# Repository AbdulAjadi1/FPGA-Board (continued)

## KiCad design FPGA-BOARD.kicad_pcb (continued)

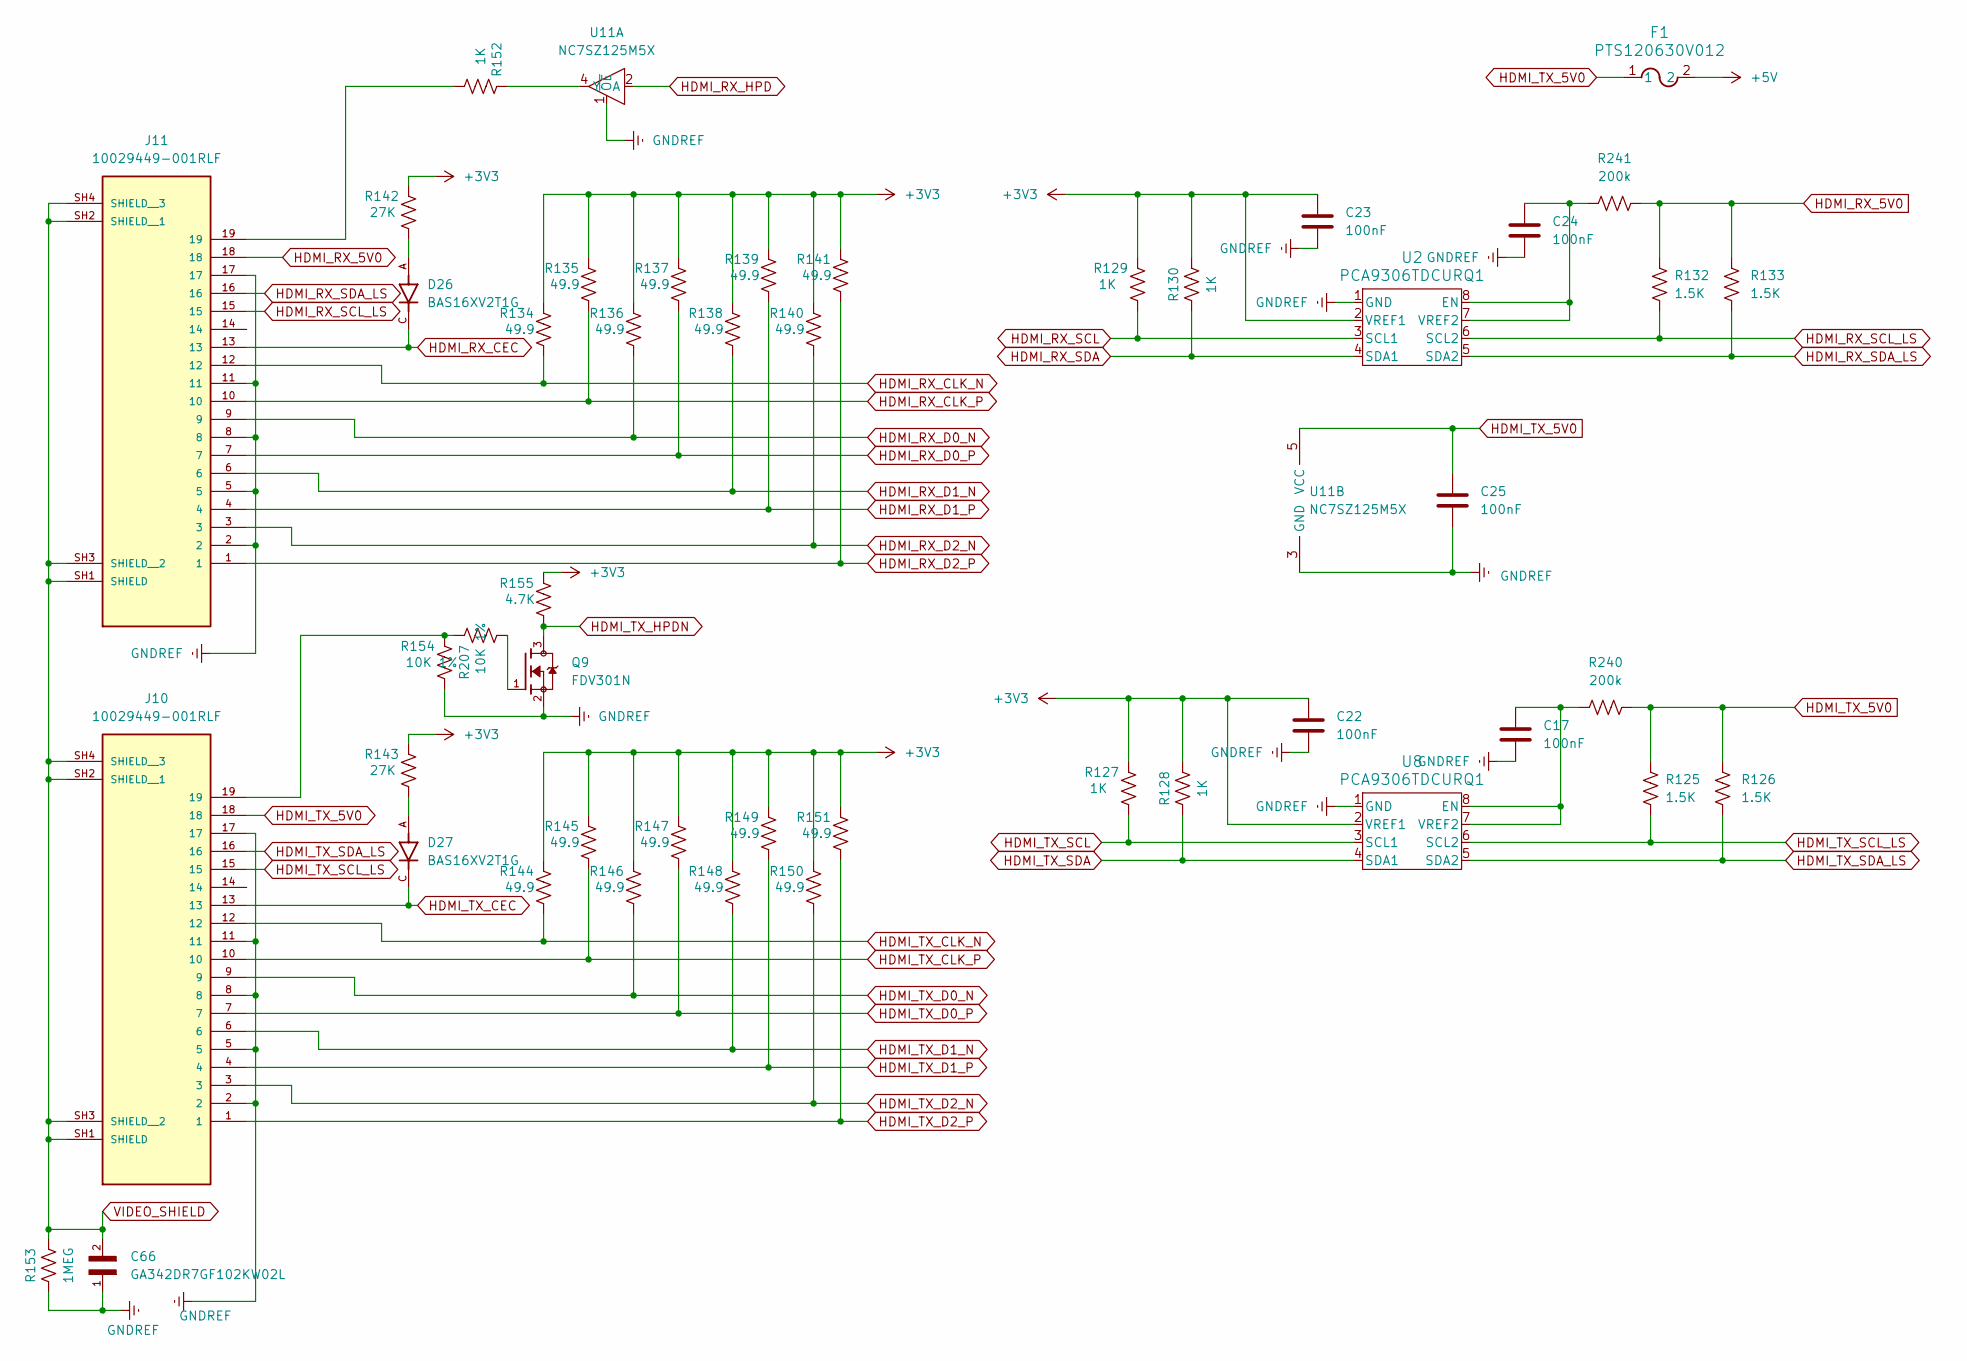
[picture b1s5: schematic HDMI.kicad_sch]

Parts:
C17, C22, C23, C24, C25: 100nF; C_0201_0603Metric; LCSC PN c307380
C66: GA342DR7GF102KW02L; CAPC4520X220N; LCSC PN C237595
D26, D27: BAS16XV2T1G; SODFL1608X70N; PARTREV 10; LCSC PN C152479
F1: PTS120630V012; LCSC PN C2442491
J10, J11: 10029449-001RLF; AMPHENOL_10029449-001RLF; PARTREV Y
Q9: FDV301N; PARTREV 8; LCSC PN C15310
R125, R126, R132, R133: 1.5K; R_0402; LCSC PN C114759
R127, R128, R129, R130, R152: 1K; R_0402; LCSC PN C106235
R134, R135, R136, R137, R138, R139, R140, R141, R144, R145, R146, R147, R148, R149, R150, R151: 49.9; R_0402; LCSC PN C87044
R142, R143: 27K; R_0402; LCSC PN C138022
R153: 1MEG; R_0402; LCSC PN C138033
R154, R207: 10K 1%; R_0402; LCSC PN C60490
R155: 4.7K; R_0201_0603Metric; LCSC PN C138135
R240, R241: 200k; R_0402; LCSC PN c114763
U2, U8: PCA9306TDCURQ1; DCU8; LCSC PN C33196
U11: NC7SZ125M5X; SC-74A_318BQ_ONS; LCSC PN C7420

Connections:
+3V3: C22.1, C23.1, R127.2, R128.2, R129.2, R130.2, R134.2, R135.2, R136.2, R137.2, R138.2, R139.2, R140.2, R141.2, R142.2, R143.2, R144.2, R145.2, R146.2, R147.2, R148.2, R149.2, R150.2, R151.2, R155.2, U2.2 (VREF1), U8.2 (VREF1); also elsewhere on the board
+5V: F1.2; also elsewhere on the board
GNDREF: C17.2, C22.2, C23.2, C24.2, C25.2, C66.1, J10.2, J10.5, J10.8, J10.11, J10.17, J11.2, J11.5, J11.8, J11.11, J11.17, Q9.2, R153.1, R154.1, U2.1 (GND), U8.1 (GND), U11.1 (~OE), U11.3 (GND); also elsewhere on the board
HDMI_RX_5V0: J11.18, R132.2, R133.2, R241.1
HDMI_RX_CEC: D26.C, J11.13; also elsewhere on the board
HDMI_RX_CLK_N: J11.12, R134.1; also elsewhere on the board
HDMI_RX_CLK_P: J11.10, R135.1; also elsewhere on the board
HDMI_RX_D0_N: J11.9, R136.1; also elsewhere on the board
HDMI_RX_D0_P: J11.7, R137.1; also elsewhere on the board
HDMI_RX_D1_N: J11.6, R138.1; also elsewhere on the board
HDMI_RX_D1_P: J11.4, R139.1; also elsewhere on the board
HDMI_RX_D2_N: J11.3, R140.1; also elsewhere on the board
HDMI_RX_D2_P: J11.1, R141.1; also elsewhere on the board
HDMI_RX_HPD: U11.2 (A); also elsewhere on the board
HDMI_RX_SCL: R129.1, U2.3 (SCL1); also elsewhere on the board
HDMI_RX_SCL_LS: J11.15, R132.1, U2.6 (SCL2)
HDMI_RX_SDA: R130.1, U2.4 (SDA1); also elsewhere on the board
HDMI_RX_SDA_LS: J11.16, R133.1, U2.5 (SDA2)
HDMI_TX_5V0: C25.1, F1.1, J10.18, R125.2, R126.2, R240.1, U11.5 (VCC)
HDMI_TX_CEC: D27.C, J10.13; also elsewhere on the board
HDMI_TX_CLK_N: J10.12, R144.1; also elsewhere on the board
HDMI_TX_CLK_P: J10.10, R145.1; also elsewhere on the board
HDMI_TX_D0_N: J10.9, R146.1; also elsewhere on the board
HDMI_TX_D0_P: J10.7, R147.1; also elsewhere on the board
HDMI_TX_D1_N: J10.6, R148.1; also elsewhere on the board
HDMI_TX_D1_P: J10.4, R149.1; also elsewhere on the board
HDMI_TX_D2_N: J10.3, R150.1; also elsewhere on the board
HDMI_TX_D2_P: J10.1, R151.1; also elsewhere on the board
HDMI_TX_HPDN: Q9.3, R155.1; also elsewhere on the board
HDMI_TX_SCL: R127.1, U8.3 (SCL1); also elsewhere on the board
HDMI_TX_SCL_LS: J10.15, R125.1, U8.6 (SCL2)
HDMI_TX_SDA: R128.1, U8.4 (SDA1); also elsewhere on the board
HDMI_TX_SDA_LS: J10.16, R126.1, U8.5 (SDA2)
unnamed: D26.A, R142.1
unnamed: D27.A, R143.1
unnamed: J10.19, R154.2, R207.2
unnamed: J11.19, R152.1
unnamed: Q9.1, R207.1
unnamed: C24.1, R241.2, U2.7 (VREF2), U2.8 (EN)
unnamed: C17.1, R240.2, U8.7 (VREF2), U8.8 (EN)
unnamed: R152.2, U11.4 (Y)
VIDEO_SHIELD: C66.2, J10.SH1 (SHIELD), J10.SH2 (SHIELD__1), J10.SH3 (SHIELD__2), J10.SH4 (SHIELD__3), J11.SH1 (SHIELD), J11.SH2 (SHIELD__1), J11.SH3 (SHIELD__2), J11.SH4 (SHIELD__3), R153.2

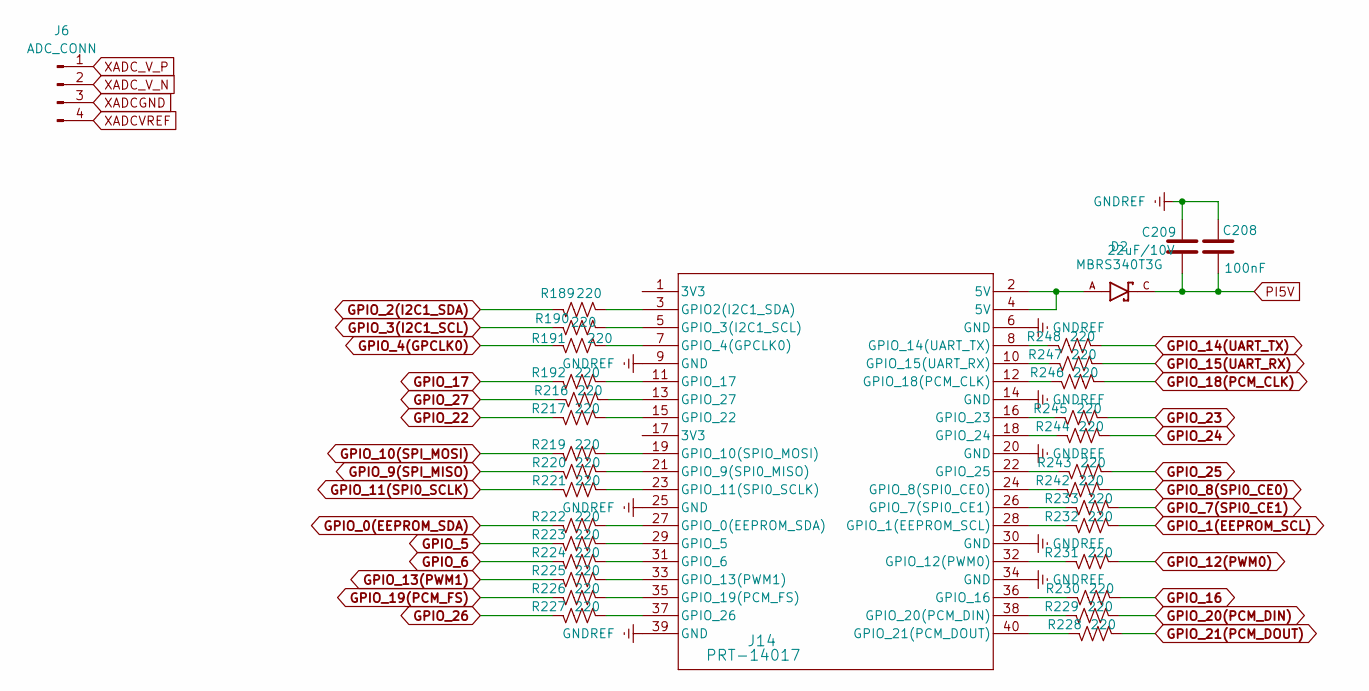
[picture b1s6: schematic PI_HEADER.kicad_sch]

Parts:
C208: 100nF; C_0201_0603Metric; LCSC PN c307380
C209: 22uF/10V; C_0805; LCSC PN C602037
D2: MBRS340T3G; DIOM7959X261N; PARTREV 14; LCSC PN C40326
J6: ADC_CONN; PinSocket_1x04_P2.54mm_Vertical
J14: PRT-14017; CONN_PRT-14017_SPK
R189, R190, R191, R192, R216, R217, R219, R220, R221, R222, R223, R224, R225, R226, R227, R228, R229, R230, R231, R232, R233, R242, R243, R244, R245, R246, R247, R248: 220; R_0402; LCSC PN C112291

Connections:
GNDREF: C208.1, C209.1, J14.6 (GND), J14.9 (GND), J14.14 (GND), J14.20 (GND), J14.25 (GND), J14.30 (GND), J14.34 (GND), J14.39 (GND); also elsewhere on the board
GPIO_0(EEPROM_SDA): R222.1; also elsewhere on the board
GPIO_1(EEPROM_SCL): R232.2; also elsewhere on the board
GPIO_2(I2C1_SDA): R189.1; also elsewhere on the board
GPIO_3(I2C1_SCL): R190.1; also elsewhere on the board
GPIO_4(GPCLK0): R191.1; also elsewhere on the board
GPIO_5: R223.1; also elsewhere on the board
GPIO_6: R224.1; also elsewhere on the board
GPIO_7(SPI0_CE1): R233.2; also elsewhere on the board
GPIO_8(SPI0_CE0): R242.2; also elsewhere on the board
GPIO_9(SPI_MISO): R220.1; also elsewhere on the board
GPIO_10(SPI_MOSI): R219.1; also elsewhere on the board
GPIO_11(SPI0_SCLK): R221.1; also elsewhere on the board
GPIO_12(PWM0): R231.2; also elsewhere on the board
GPIO_13(PWM1): R225.1; also elsewhere on the board
GPIO_14(UART_TX): R248.2; also elsewhere on the board
GPIO_15(UART_RX): R247.2; also elsewhere on the board
GPIO_16: R230.2; also elsewhere on the board
GPIO_17: R192.1; also elsewhere on the board
GPIO_18(PCM_CLK): R246.2; also elsewhere on the board
GPIO_19(PCM_FS): R226.1; also elsewhere on the board
GPIO_20(PCM_DIN): R229.2; also elsewhere on the board
GPIO_21(PCM_DOUT): R228.2; also elsewhere on the board
GPIO_22: R217.1; also elsewhere on the board
GPIO_23: R245.2; also elsewhere on the board
GPIO_24: R244.2; also elsewhere on the board
GPIO_25: R243.2; also elsewhere on the board
GPIO_26: R227.1; also elsewhere on the board
GPIO_27: R216.1; also elsewhere on the board
unnamed: D2.A, J14.2 (5V), J14.4 (5V)
unnamed: J14.3 (GPIO2(I2C1_SDA)), R189.2
unnamed: J14.27 (GPIO_0(EEPROM_SDA)), R222.2
unnamed: J14.28 (GPIO_1(EEPROM_SCL)), R232.1
unnamed: J14.5 (GPIO_3(I2C1_SCL)), R190.2
unnamed: J14.7 (GPIO_4(GPCLK0)), R191.2
unnamed: J14.29 (GPIO_5), R223.2
unnamed: J14.31 (GPIO_6), R224.2
unnamed: J14.26 (GPIO_7(SPI0_CE1)), R233.1
unnamed: J14.24 (GPIO_8(SPI0_CE0)), R242.1
unnamed: J14.21 (GPIO_9(SPI0_MISO)), R220.2
unnamed: J14.19 (GPIO_10(SPIO_MOSI)), R219.2
unnamed: J14.23 (GPIO_11(SPI0_SCLK)), R221.2
unnamed: J14.32 (GPIO_12(PWM0)), R231.1
unnamed: J14.33 (GPIO_13(PWM1)), R225.2
unnamed: J14.8 (GPIO_14(UART_TX)), R248.1
unnamed: J14.10 (GPIO_15(UART_RX)), R247.1
unnamed: J14.36 (GPIO_16), R230.1
unnamed: J14.11 (GPIO_17), R192.2
unnamed: J14.12 (GPIO_18(PCM_CLK)), R246.1
unnamed: J14.35 (GPIO_19(PCM_FS)), R226.2
unnamed: J14.38 (GPIO_20(PCM_DIN)), R229.1
unnamed: J14.40 (GPIO_21(PCM_DOUT)), R228.1
unnamed: J14.15 (GPIO_22), R217.2
unnamed: J14.16 (GPIO_23), R245.1
unnamed: J14.18 (GPIO_24), R244.1
unnamed: J14.22 (GPIO_25), R243.1
unnamed: J14.37 (GPIO_26), R227.2
unnamed: J14.13 (GPIO_27), R216.2
PI5V: C208.2, C209.2, D2.C; also elsewhere on the board
XADCGND: J6.3; also elsewhere on the board
XADCVREF: J6.4; also elsewhere on the board
XADC_V_N: J6.2; also elsewhere on the board
XADC_V_P: J6.1; also elsewhere on the board

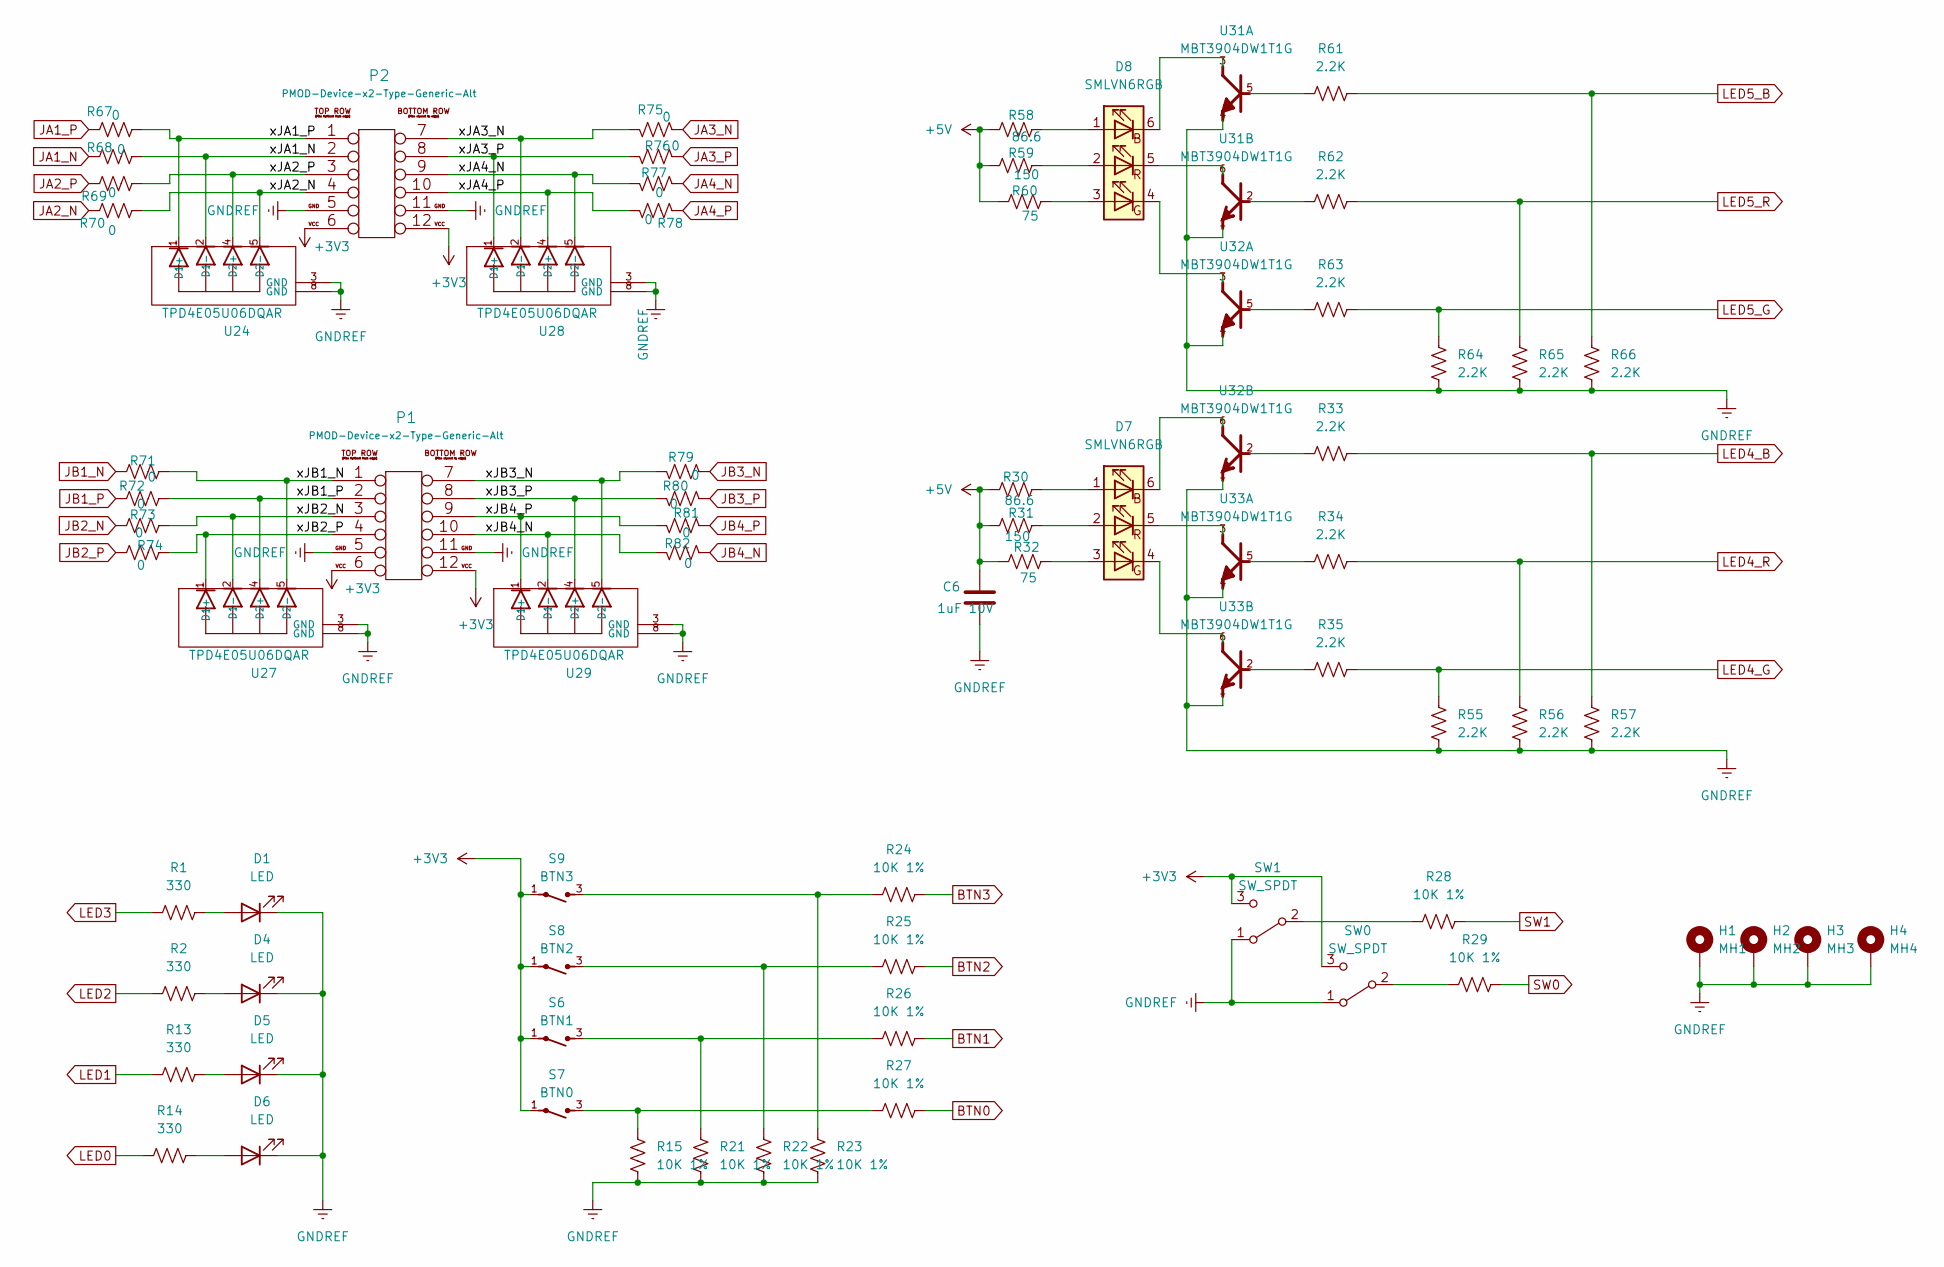
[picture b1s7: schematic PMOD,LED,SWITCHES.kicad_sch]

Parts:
C6: 1uF 10V; C_0402; LCSC PN C52923
D1, D4, D5, D6: LED; LED_0402_1005Metric; LCSC PN C130723
D7, D8: SMLVN6RGB; LED_SMLV56_ROM; LCSC PN C20110230
H1: MH1; MountingHole_2.2mm_M2_Pad
H2: MH2; MountingHole_2.2mm_M2_Pad
H3: MH3; MountingHole_2.2mm_M2_Pad
H4: MH4; MountingHole_2.2mm_M2_Pad
P1, P2: PMOD-Device-x2-Type-Generic-Alt; CONN_PPPC062LJBN-RC_SUL
R1, R2, R13, R14: 330; R_0402; LCSC PN C105875
R15, R21, R22, R23, R24, R25, R26, R27, R28, R29: 10K 1%; R_0402; LCSC PN C60490
R30, R58: 86.6; R_0402; LCSC PN C830266
R31, R59: 150; R_0402; LCSC PN C138054
R32, R60: 75; R_0402; LCSC PN C114757
R33, R34, R35, R55, R56, R57, R61, R62, R63, R64, R65, R66: 2.2K; R_0402; LCSC PN c114762
R67, R68, R69, R70, R71, R72, R73, R74, R75, R76, R77, R78, R79, R80, R81, R82: 0; R_0402; LCSC PN C106231
S6: BTN1; TS-1002S-050xxC_XNP; LCSC PN C455110
S7: BTN0; TS-1002S-050xxC_XNP; LCSC PN C455110
S8: BTN2; TS-1002S-050xxC_XNP; LCSC PN C455110
S9: BTN3; TS-1002S-050xxC_XNP; LCSC PN C455110
SW0, SW1: SW_SPDT; SW_EG1218
U24, U27, U28, U29: TPD4E05U06DQAR; IC_TPD4E05U06DQAR; PARTREV N; LCSC PN C138714
U31, U32, U33: MBT3904DW1T1G; SOT236; LCSC PN C110150

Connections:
+3V3: P1.6, P1.12, P2.6, P2.12, S6.1, S7.1, S8.1, S9.1, SW0.3 (C), SW1.3 (C); also elsewhere on the board
+5V: C6.1, R30.1, R31.1, R32.1, R58.1, R59.1, R60.1; also elsewhere on the board
/PMOD, LED, SWITCHES/xJA1_N: P2.2, R68.2, U24.2 (D1-)
/PMOD, LED, SWITCHES/xJA1_P: P2.1, R67.2, U24.1 (D1+)
/PMOD, LED, SWITCHES/xJA2_N: P2.4, R70.2, U24.5 (D2-)
/PMOD, LED, SWITCHES/xJA2_P: P2.3, R69.2, U24.4 (D2+)
/PMOD, LED, SWITCHES/xJA3_N: P2.7, R75.2, U28.2 (D1-)
/PMOD, LED, SWITCHES/xJA3_P: P2.8, R76.2, U28.1 (D1+)
/PMOD, LED, SWITCHES/xJA4_N: P2.9, R77.2, U28.5 (D2-)
/PMOD, LED, SWITCHES/xJA4_P: P2.10, R78.2, U28.4 (D2+)
/PMOD, LED, SWITCHES/xJB1_N: P1.1, R71.2, U27.5 (D2-)
/PMOD, LED, SWITCHES/xJB1_P: P1.2, R72.2, U27.4 (D2+)
/PMOD, LED, SWITCHES/xJB2_N: P1.3, R73.2, U27.2 (D1-)
/PMOD, LED, SWITCHES/xJB2_P: P1.4, R74.2, U27.1 (D1+)
/PMOD, LED, SWITCHES/xJB3_N: P1.7, R79.2, U29.5 (D2-)
/PMOD, LED, SWITCHES/xJB3_P: P1.8, R80.2, U29.4 (D2+)
/PMOD, LED, SWITCHES/xJB4_N: P1.10, R82.2, U29.2 (D1-)
/PMOD, LED, SWITCHES/xJB4_P: P1.9, R81.2, U29.1 (D1+)
BTN0: R27.2; also elsewhere on the board
BTN1: R26.2; also elsewhere on the board
BTN2: R25.2; also elsewhere on the board
BTN3: R24.2; also elsewhere on the board
GNDREF: C6.2, D1.1 (K), D4.1 (K), D5.1 (K), D6.1 (K), H1.1, H2.1, H3.1, H4.1, P1.5, P1.11, P2.5, P2.11, R15.2, R21.2, R22.2, R23.2, R55.1, R56.1, R57.1, R64.1, R65.1, R66.1, SW0.1 (A), SW1.1 (A), U24.3 (GND), U24.8 (GND), U27.3 (GND), U27.8 (GND), U28.3 (GND), U28.8 (GND), U29.3 (GND), U29.8 (GND), U31.1, U31.4, U32.1, U32.4, U33.1, U33.4; also elsewhere on the board
JA1_N: R68.1; also elsewhere on the board
JA1_P: R67.1; also elsewhere on the board
JA2_N: R70.1; also elsewhere on the board
JA2_P: R69.1; also elsewhere on the board
JA3_N: R75.1; also elsewhere on the board
JA3_P: R76.1; also elsewhere on the board
JA4_N: R77.1; also elsewhere on the board
JA4_P: R78.1; also elsewhere on the board
JB1_N: R71.1; also elsewhere on the board
JB1_P: R72.1; also elsewhere on the board
JB2_N: R73.1; also elsewhere on the board
JB2_P: R74.1; also elsewhere on the board
JB3_N: R79.1; also elsewhere on the board
JB3_P: R80.1; also elsewhere on the board
JB4_N: R82.1; also elsewhere on the board
JB4_P: R81.1; also elsewhere on the board
LED0: R14.1; also elsewhere on the board
LED1: R13.1; also elsewhere on the board
LED2: R2.1; also elsewhere on the board
LED3: R1.1; also elsewhere on the board
LED4_B: R33.2, R57.2; also elsewhere on the board
LED4_G: R35.2, R55.2; also elsewhere on the board
LED4_R: R34.2, R56.2; also elsewhere on the board
LED5_B: R61.2, R66.2; also elsewhere on the board
LED5_G: R63.2, R64.2; also elsewhere on the board
LED5_R: R62.2, R65.2; also elsewhere on the board
unnamed: D1.2 (A), R1.2
unnamed: D4.2 (A), R2.2
unnamed: D5.2 (A), R13.2
unnamed: D6.2 (A), R14.2
unnamed: D7.1 (BA), R30.2
unnamed: D7.6 (BK), U32.6
unnamed: D7.3 (GA), R32.2
unnamed: D7.4 (GK), U33.6
unnamed: D7.2 (RA), R31.2
unnamed: D7.5 (RK), U33.3
unnamed: D8.1 (BA), R58.2
unnamed: D8.6 (BK), U31.3
unnamed: D8.3 (GA), R60.2
unnamed: D8.4 (GK), U32.3
unnamed: D8.2 (RA), R59.2
unnamed: D8.5 (RK), U31.6
unnamed: R15.1, R27.1, S7.3
unnamed: R21.1, R26.1, S6.3
unnamed: R22.1, R25.1, S8.3
unnamed: R23.1, R24.1, S9.3
unnamed: R33.1, U32.2
unnamed: R34.1, U33.5
unnamed: R35.1, U33.2
unnamed: R61.1, U31.5
unnamed: R62.1, U31.2
unnamed: R63.1, U32.5
unnamed: R29.1, SW0.2 (B)
unnamed: R28.1, SW1.2 (B)
SW0: R29.2; also elsewhere on the board
SW1: R28.2; also elsewhere on the board

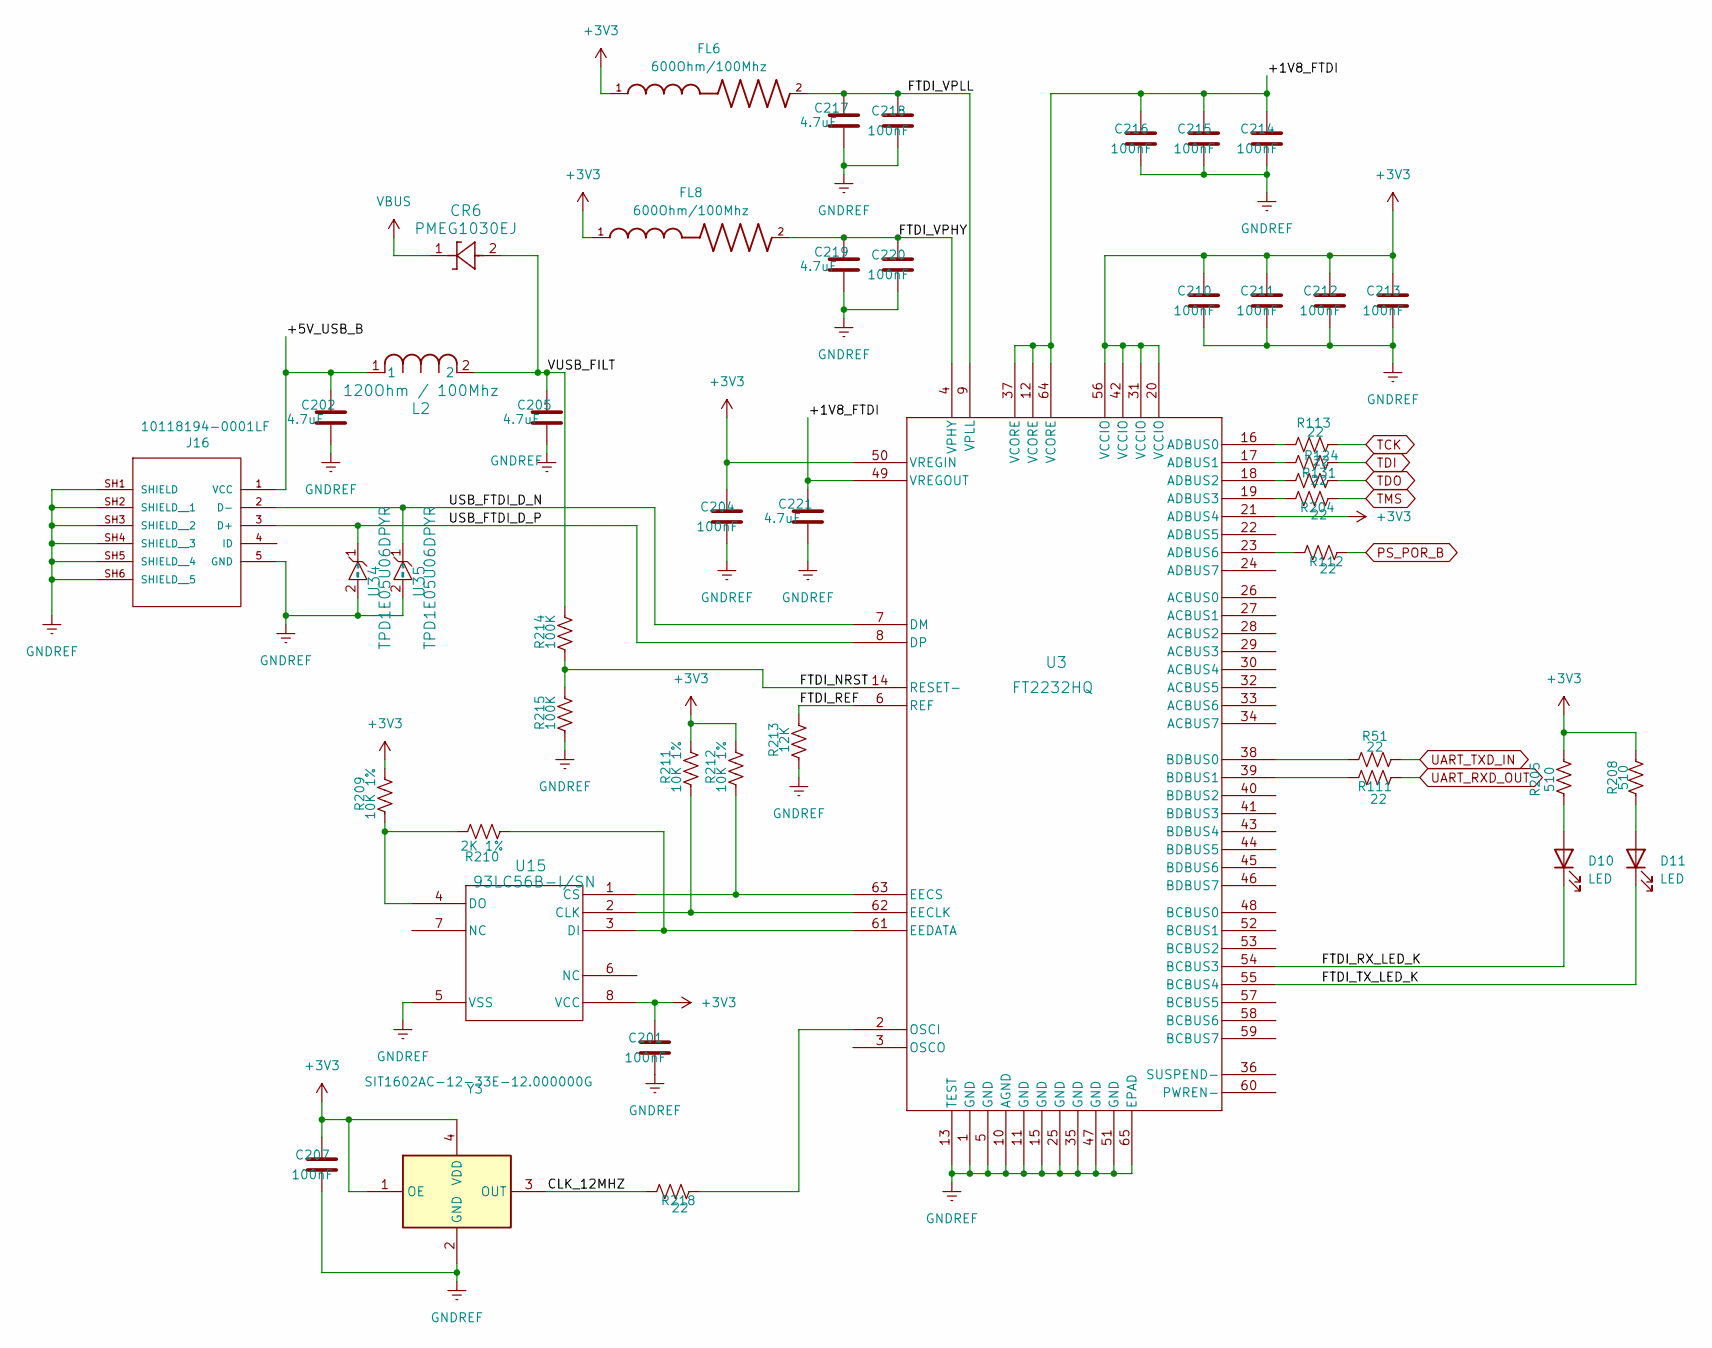
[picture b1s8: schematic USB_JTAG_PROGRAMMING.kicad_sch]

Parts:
C201, C204, C207, C210, C211, C212, C213, C214, C215, C216, C218, C220: 100nF; C_0201_0603Metric; LCSC PN c307380
C202, C205, C217, C219, C221: 4.7uF; C_0402; LCSC PN C2858031
CR6: PMEG1030EJ; SOD323F_NXP; LCSC PN C133633
D10, D11: LED; LED_0402_1005Metric; LCSC PN C130723
FL6, FL8: 600Ohm/100Mhz; BEADC1608X95N; LCSC PN C19330
J16: 10118194-0001LF; AMPHENOL_10118194-0001LF; PARTREV D
L2: 120Ohm / 100Mhz; IND_BLM18_0603_MUR; LCSC PN C14709
R51, R111, R112, R113, R124, R131, R204, R218: 22; R_0201_0603Metric; LCSC PN C270355
R205, R208: 510; R_0201_0603Metric; LCSC PN C18164337
R209, R211, R212: 10K 1%; R_0402; LCSC PN C60490
R210: 2K 1%; R_0402; LCSC PN C60488
R213: 12K; R_0201_0603Metric; LCSC PN C2092166
R214, R215: 100K; R_0402; LCSC PN C60491
U3: FT2232HQ; 64QFN_FT2232HQ_FTD; LCSC PN C3025148
U15: 93LC56B-I/SN; SOIC8-N_MC_MCH; LCSC PN C183620
U34, U35: TPD1E05U06DPYR; DIO_TPD1E05U06DPYR; LCSC PN C436349
Y3: SIT1602AC-12-33E-12.000000G; SIT1602AC1233E12000000G; Mouser Part Number 788-1602AC1233E12.G

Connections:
+3V3: C201.1, C204.1, C207.1, C210.1, C211.1, C212.1, C213.1, FL6.1, FL8.1, R205.2, R208.2, R209.2, R211.2, R212.2, U3.20 (VCCIO), U3.21 (ADBUS4), U3.31 (VCCIO), U3.42 (VCCIO), U3.50 (VREGIN), U3.56 (VCCIO), U15.8 (VCC), Y3.1 (OE), Y3.4 (VDD); also elsewhere on the board
/USB_JTAG_PROGRAMMING/+1V8_FTDI: C214.1, C215.1, C216.1, C221.1, U3.12 (VCORE), U3.37 (VCORE), U3.49 (VREGOUT), U3.64 (VCORE)
/USB_JTAG_PROGRAMMING/+5V_USB_B: C202.1, J16.1 (VCC), L2.1
/USB_JTAG_PROGRAMMING/CLK_12MHZ: R218.1, Y3.3 (OUT)
/USB_JTAG_PROGRAMMING/FTDI_NRST: R214.1, R215.2, U3.14 (RESET-)
/USB_JTAG_PROGRAMMING/FTDI_REF: R213.2, U3.6 (REF)
/USB_JTAG_PROGRAMMING/FTDI_RX_LED_K: D10.1 (K), U3.54 (BCBUS3)
/USB_JTAG_PROGRAMMING/FTDI_TX_KED_K: D11.1 (K), U3.55 (BCBUS4)
/USB_JTAG_PROGRAMMING/FTDI_VPHY: C219.1, C220.1, FL8.2, U3.4 (VPHY)
/USB_JTAG_PROGRAMMING/FTDI_VPLL: C217.1, C218.1, FL6.2, U3.9 (VPLL)
/USB_JTAG_PROGRAMMING/USB_FTDI_D_N: J16.2 (D-), U3.7 (DM), U35.1 (I/O)
/USB_JTAG_PROGRAMMING/USB_FTDI_D_P: J16.3 (D+), U3.8 (DP), U34.1 (I/O)
/USB_JTAG_PROGRAMMING/VUSB_FILT: C205.1, CR6.2, L2.2, R214.2
GNDREF: C201.2, C202.2, C204.2, C205.2, C207.2, C210.2, C211.2, C212.2, C213.2, C214.2, C215.2, C216.2, C217.2, C218.2, C219.2, C220.2, C221.2, J16.5 (GND), J16.SH1 (SHIELD), J16.SH2 (SHIELD__1), J16.SH3 (SHIELD__2), J16.SH4 (SHIELD__3), J16.SH5 (SHIELD__4), J16.SH6 (SHIELD__5), R213.1, R215.1, U3.1 (GND), U3.5 (GND), U3.10 (AGND), U3.11 (GND), U3.13 (TEST), U3.15 (GND), U3.25 (GND), U3.35 (GND), U3.47 (GND), U3.51 (GND), U3.65 (EPAD), U15.5 (VSS), U34.2 (GND), U35.2 (GND), Y3.2 (GND); also elsewhere on the board
unnamed: D10.2 (A), R205.1
unnamed: D11.2 (A), R208.1
unnamed: R113.1, U3.16 (ADBUS0)
unnamed: R124.1, U3.17 (ADBUS1)
unnamed: R131.1, U3.18 (ADBUS2)
unnamed: R204.1, U3.19 (ADBUS3)
unnamed: R112.1, U3.23 (ADBUS6)
unnamed: R51.1, U3.38 (BDBUS0)
unnamed: R111.1, U3.39 (BDBUS1)
unnamed: R218.2, U3.2 (OSCI)
unnamed: R211.1, U3.62 (EECLK), U15.2 (CLK)
unnamed: R212.1, U3.63 (EECS), U15.1 (CS)
unnamed: R210.1, U3.61 (EEDATA), U15.3 (DI)
unnamed: R209.1, R210.2, U15.4 (DO)
PS_POR_B: R112.2; also elsewhere on the board
TCK: R113.2; also elsewhere on the board
TDI: R124.2; also elsewhere on the board
TDO: R131.2; also elsewhere on the board
TMS: R204.2; also elsewhere on the board
UART_RXD_OUT: R111.2; also elsewhere on the board
UART_TXD_IN: R51.2; also elsewhere on the board
VBUS: CR6.1; also elsewhere on the board

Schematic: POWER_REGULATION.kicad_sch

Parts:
C7, C20, C27: 4.7uF; C_0402; LCSC PN C2858031
C18, C19, C28, C32, C199, C234: 100nF; C_0201_0603Metric; LCSC PN c307380
C21: 1uF 10V; C_0402; LCSC PN C52923
C26: 470nF; C_0201_0603Metric; LCSC PN C5383023
C29: 22nF; C_0402; LCSC PN c337699
C30: 100nF 10V; C_0402; LCSC PN C77020
C31, C192, C193, C194, C195, C196, C197, C198: 10uF 10V; C_0805; LCSC PN C15850
CR7: BZT52C12-7-F; SOD123_DIO; LCSC PN C19077410
D37: SMBJ15CA-E3_52; DIOM5436X244N; Manufacturer_Part_Number SMBJ15CA-E3/52; LCSC PN C435933
FL2, FL5, FL9: 600Ohm/100Mhz; BEADC1608X95N; LCSC PN C19330
J1: PJ-102AH; CUI_PJ-102AH
J2: GND; PinHeader_1x01_P2.54mm_Vertical
J3: Conn_01x03_Pin; PinHeader_1x03_P2.54mm_Vertical
J17: Conn_01x02_Pin; PinHeader_1x02_P2.54mm_Vertical
J18: +3V3; PinHeader_1x01_P2.54mm_Vertical
J20: +1V5; PinHeader_1x01_P2.54mm_Vertical
J21: +1V0; PinHeader_1x01_P2.54mm_Vertical
J22: VCC_1V8IO; PinHeader_1x01_P2.54mm_Vertical
L4: NR5040T2R2N/2.2uH; IND_TAIYO_NR5040_TAY; LCSC PN C223063
Q7: DMG2305UX-13; DMG2305UX_13; PARTREV 09/2018; LCSC PN C144153
R83: 100K; R_0402; LCSC PN C60491
R84: 4.7k; R_0402; LCSC PN C105871
R85: 20K 1%; R_0402; LCSC PN C93942
R86, R89: 10K 1%; R_0402; LCSC PN C60490
R87: 13.3K/1%; R_0402; LCSC PN C274352
R88: 69.8K/1%; R_0402; LCSC PN C5126210
R90: 62k/1%; R_0402; LCSC PN C137950
R91: 0; R_0402; LCSC PN C106231
U14: TLV62130RGTT; LCSC PN C122479
U16: REF3012; SOT-23; LCSC PN C34674

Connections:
+1V0: J21.1; also elsewhere on the board
+1V5: J20.1; also elsewhere on the board
+1V8: C21.1, FL2.1; also elsewhere on the board
+3V3: C7.1, C19.1, FL9.1, J18.1; also elsewhere on the board
+5V: J3.2, J17.1, R85.1; also elsewhere on the board
/POWER_REGULATION/VUSB: J3.3, Q7.3
AVCC3V3: C20.1, C199.1, C234.1, FL9.2; also elsewhere on the board
EN_1: R85.2, R86.1; also elsewhere on the board
GNDREF: C7.2, C19.2, C20.2, C21.2, C28.2, C29.2, C30.2, C31.2, C192.2, C193.2, C194.2, C195.2, C196.2, C197.2, C198.2, C199.2, C234.2, D37.2, FL5.1, J1.2, J1.3, J2.1, R84.2, R86.2, R87.2, R89.2, U14.6 (AGND), U14.8 (DEF), U14.15 (PGND@1), U14.16 (PGND@2), U14.17 (GND), U14.18, U14.19, U14.20, U14.21, U14.22; also elsewhere on the board
unnamed: C27.2, CR7.2, Q7.1, R83.2, R84.1
unnamed: C28.1, R89.1, R90.2, U14.13 (EN)
unnamed: R87.1, R88.2, U14.5 (FB)
unnamed: R91.2, U14.7 (FSW)
unnamed: C29.1, U14.9 (SS/TR)
unnamed: L4.2, U14.1 (SW@1), U14.2 (SW@2), U14.3 (SW@3)
PI5V: J17.2; also elsewhere on the board
REG5V0: C31.1, J3.1, L4.1, R88.1, R91.1, U14.14 (VOS)
VBUS: C27.1, CR7.1, Q7.2, R83.1; also elsewhere on the board
VCC1V8_IO: J22.1; also elsewhere on the board
VU: C30.1, C192.1, C193.1, C194.1, C195.1, C196.1, C197.1, C198.1, D37.1, J1.1, R90.1, U14.10 (AVIN), U14.11 (PVIN@1), U14.12 (PVIN@2)
XADC1V8: C26.1, C32.1, FL2.2, U16.1 (IN)
XADCGND: C18.2, C26.2, C32.2, FL5.2, U16.3 (GND); also elsewhere on the board
XADCVREF: C18.1, U16.2 (OUT); also elsewhere on the board

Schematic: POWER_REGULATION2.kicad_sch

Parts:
C33, C155, C162, C165, C168, C171, C174: 100nF; C_0201_0603Metric; LCSC PN c307380
C81, C146, C172: 4.7uF; C_0402; LCSC PN C2858031
C139, C140, C141, C142, C156, C164, C167, C170, C200: 22uF/10V; C_0805; LCSC PN C602037
C143: 10uF 10V; C_0805; LCSC PN C15850
C144, C173, C203: 1uF 10V; C_0402; LCSC PN C52923
C145: 3.3uF/10V; C_0603; LCSC PN C528975
C147: 1.5nF; C_0201_0603Metric; LCSC PN C2184288
C148, C154, C157, C160: 33nF; C_0201_0603Metric; LCSC PN C161475
C149, C151, C153, C159, C161, C163, C166, C169: 10pF; C_0201_0603Metric; LCSC PN C76921
C150: 150pF; C_0201_0603Metric; LCSC PN C3843470
C152: 1.2nF; C_0201_0603Metric; LCSC PN C913747
C158: 330pF; C_0201_0603Metric; LCSC PN C2184280
CR2: 1SS352; USC_TOS; LCSC PN C15885
D3: LED; LED_0402_1005Metric; LCSC PN C130719
L3: NR5040T2R2N/2.2uH; IND_TAIYO_NR5040_TAY; LCSC PN C223063
L5: SRP6540-1R5M 1.5uH; IND_SRP6540-1R5M; LCSC PN C3223801
L6, L7: NR5040T4R7N/ 4.7uH; IND_TAIYO_NR5040_TAY; LCSC PN C223064
Q8: FDV301N; PARTREV 8; LCSC PN C15310
R92, R187: 15K; R_0402; LCSC PN C114761
R93: 4.7k; R_0402; LCSC PN C105871
R94: 680; R_0201_0603Metric; LCSC PN C158391
R97: 33K; R_0402; LCSC PN C138003
R98: 100K; R_0402; LCSC PN C60491
R99, R206: 10K 1%; R_0402; LCSC PN C60490
R100: 180K; R_0402; LCSC PN C138046
R101: 75K; R_0402; LCSC PN C137935
R102: 150K; R_0402; LCSC PN C93947
R103: 8.87K/1%; R_0402; LCSC PN C48391747
R104, R108: 10.2K/1%; R_0402; LCSC PN C138069
R105: 20K 1%; R_0402; LCSC PN C93942
R106: 16K/1%; R_0402; LCSC PN C163487
R107: 31.6K/1%; R_0402; LCSC PN C276265
R109: 8.2K/1%; R_0402; LCSC PN C137929
R110: 30K/1%; R_0402; LCSC PN C138008
R188: 82; R_0402; LCSC PN C163453
S1: PTS645SK50SMTR92LFS; SW_PTS645SK50SMTR92LFS; LCSC PN C221872
U9: SIP32510DT-T1-GE3; SIP32510DT-T1-GE3_VIS
U19: NL17SZ17XV5T2G; SOT553-5_ONS; LCSC PN C152502
U21: NC7WZ07P6X; MPN NC7WZ07P6X; LCSC PN C95342
U22: TPS65400RGZT; RGZ0048B; PARTREV D; LCSC PN C201658
U40: TPS22918DBVR; DBV6_TEX; LCSC PN C131941

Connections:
+1V0: C169.1, C170.1, L3.1, R109.1; also elsewhere on the board
+1V5: C156.1, C161.1, L7.1, R103.1; also elsewhere on the board
+1V8: C163.1, C164.1, C172.1, C173.1, L6.1, R105.1, U9.5 (IN), U9.6 (IN), U40.1 (VIN); also elsewhere on the board
+3V3: C33.1, C166.1, C167.1, C200.1, D3.2 (A), L5.1, R92.1, R93.1, R107.1, U19.5 (VCC); also elsewhere on the board
+5V: C139.1, C140.1, C141.1, C142.1, C144.1, U22.5 (PVIN1), U22.6 (PVIN2), U22.22 (VIN), U22.30 (PVIN3), U22.31 (PVIN4); also elsewhere on the board
CE: U22.23 (CE)
EN_1: U22.13 (ENSW2), U22.27 (ENSW3), U22.34 (ENSW4), U22.48 (ENSW1/ENSEQ); also elsewhere on the board
GNDREF: C33.2, C81.2, C139.2, C140.2, C141.2, C142.2, C143.1, C144.2, C145.2, C146.2, C147.1, C148.1, C149.1, C150.1, C151.1, C152.1, C153.1, C154.1, C156.2, C157.1, C158.1, C159.1, C160.1, C164.2, C167.2, C170.2, C171.2, C172.2, C173.2, C174.2, C200.2, C203.2, Q8.2, R102.1, R104.2, R106.2, R108.2, R110.2, R188.2, R206.1, S1.3, U9.4 (GND), U19.3 (GND), U22.7 (PGND1), U22.8 (PGND2), U22.21 (AGND), U22.49 (PGND), U22.V, U40.2 (GND), U40.4 (CT), U40.5 (QOD); also elsewhere on the board
unnamed: C147.2, R97.1
unnamed: C150.2, R98.1
unnamed: C152.2, R101.1
unnamed: C158.2, R100.1
unnamed: D3.1 (K), R94.1
unnamed: Q8.3, R94.2
unnamed: C168.1, U22.1 (CB1)
unnamed: C165.1, U22.12 (CB2)
unnamed: C162.1, U22.28 (CB3)
unnamed: C155.1, U22.33 (CB4)
unnamed: C149.2, R97.2, U22.46 (COMP1)
unnamed: C151.2, R98.2, U22.15 (COMP2)
unnamed: C159.2, R100.2, U22.25 (COMP3)
unnamed: C153.2, R101.2, U22.36 (COMP4)
unnamed: R206.2, U22.38 (I2CADDR)
unnamed: R102.2, U22.40 (RCLOCK_SYNC)
unnamed: C148.2, U22.45 (SS1/PG1)
unnamed: C157.2, U22.16 (SS2/PG2)
unnamed: C160.2, U22.24 (SS3/PG3)
unnamed: C154.2, U22.37 (SS4/PG4)
unnamed: C168.2, L3.2, U22.2 (SW1), U22.3 (SW1__1), U22.4 (SW1__2)
unnamed: C165.2, L5.2, U22.9 (SW2), U22.10 (SW2__1), U22.11 (SW2__2)
unnamed: C162.2, L6.2, U22.29 (SW3)
unnamed: C155.2, L7.2, U22.32 (SW4)
unnamed: C146.1, U22.19 (VDDA)
unnamed: C143.2, U22.18 (VDDG)
unnamed: C169.2, R109.2, R110.1, U22.47 (VFB1)
unnamed: C166.2, R107.2, R108.1, U22.14 (VFB2)
unnamed: C163.2, R105.2, R106.1, U22.26 (VFB3)
unnamed: C161.2, R103.2, R104.1, U22.35 (VFB4)
PG_ALL: CR2.1, R92.2, R187.2, U9.3 (EN), U22.17 (PGOOD), U40.3 (ON)
PG_ALL_DLY: C81.1, CR2.2, R187.1, U19.2
PG_ALL_EDGE: Q8.1, U19.4, U21.3 (A2)
PS_POR_B: R93.2, S1.1, U21.4 (Y2); also elsewhere on the board
RST_N: R99.1, U22.39 (~RST)
SCL: U22.43 (SCL)
SDA: U22.42 (SDA)
VCC1V8_IO: C171.1, C174.1, C203.1, R188.1, U9.1 (OUT), U9.2 (OUT), U40.6 (VOUT); also elsewhere on the board
VDDD: C145.1, R99.2, U22.20 (VDDD)
